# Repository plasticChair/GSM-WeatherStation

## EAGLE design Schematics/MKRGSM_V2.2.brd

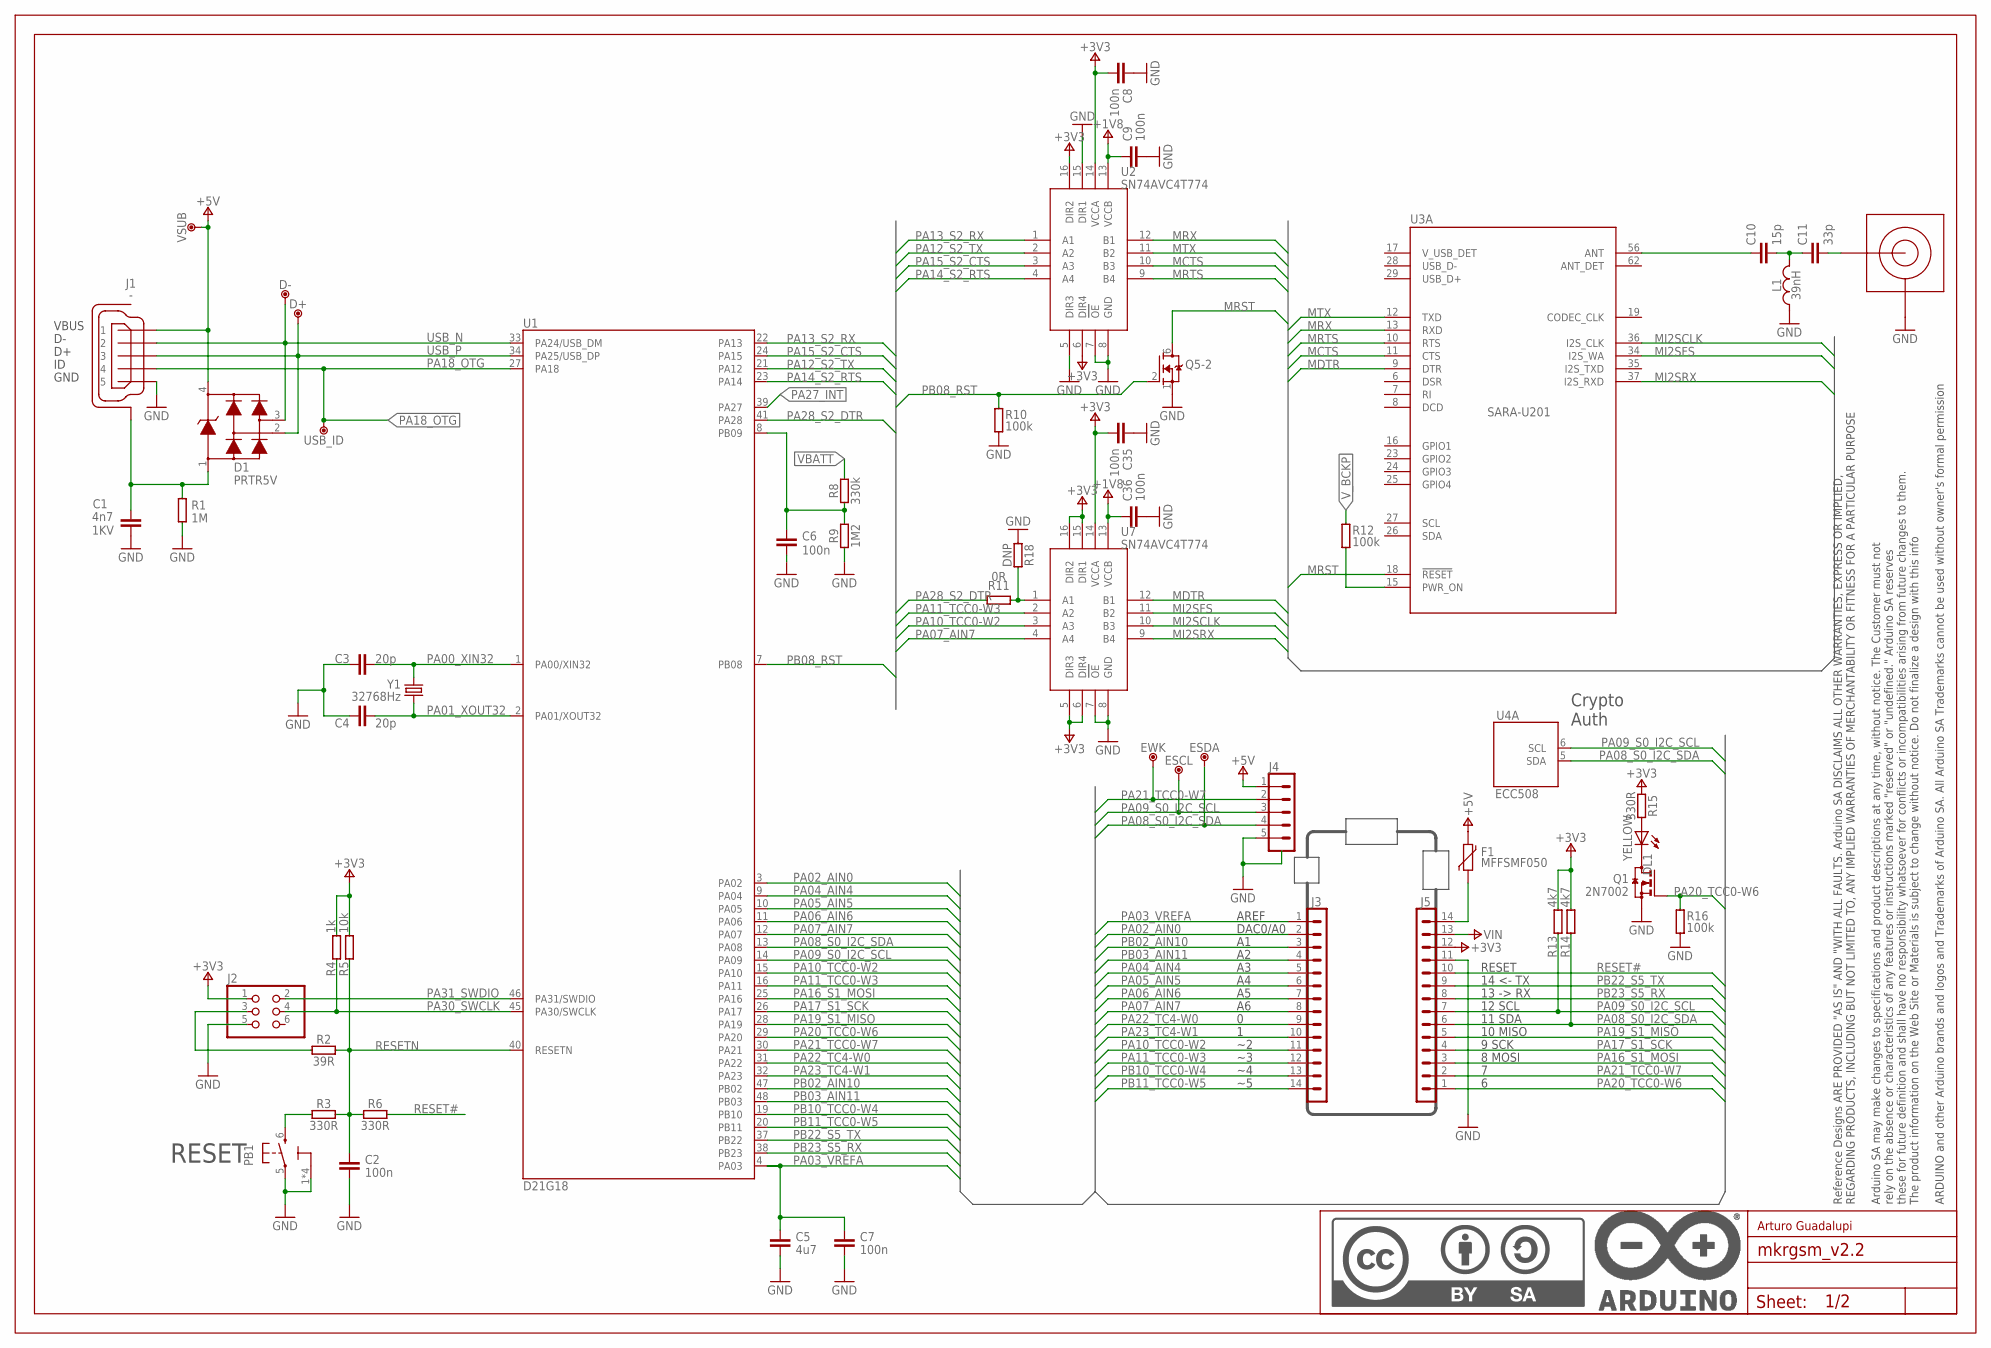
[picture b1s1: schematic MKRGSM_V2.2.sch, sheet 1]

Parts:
C1: 4n7; 0805-R2013X50N@1; VOLTAGE 1KV
C2, C6, C7, C8, C9, C35, C36: 100n; 0402-1005X55N
C3, C4: 20p; 0402-1005X55N
C5: 4u7; 0402-1005X55N
C10: 15p; 0402-1005X55N
C11: 33p; 0402-1005X55N
D1: PRTR5V; SOT190P230X110-4N
D+: DNP; TP-1.00MM
D-: DNP; TP-1.00MM
DL1: YELLOW; LEDC1608X80N-AK
ESCL: DNP; TP-1.00MM
ESDA: DNP; TP-1.00MM
EWK: DNP; TP-1.00MM
F1: MFFSMF050; 0603-1608X90N
FRAME1: DNP; FRAME
J1: -; ZX62-AB-5PA
J2: DNP; 2X3_SMT
J3, J5: -; 1X14_SMD_TH
J4: -; SM05B-SRSS-TB
J6: -; U.FL-R-SMT-1(60)
L1: 39nH; C0402
PB1: PTS820; C&K_PTS820_NO_HOLES
Q1: 2N7002; SOTFL50P160X78-3
Q5: 2N7002DW-7-FNO_PAD; PWR_SC70-6L2
R1: 1M; 0402-1005X55N
R2: 39R; 0402-1005X55N
R3, R6, R15: 330R; 0402-1005X55N
R4: 1k; 0402-1005X55N
R5: 10k; 0402-1005X55N
R8: 330k; 0402-1005X55N
R9: 1M2; 0402-1005X55N
R10, R12, R16: 100k; 0402-1005X55N
R11: 0R; 0402-1005X55N
R13, R14: 4k7; 0402-1005X55N
R18: DNP; 0402-1005X55N
U1: D21G18; QFN50P700X700X90-49XN-EPSQ515
U2, U7: SN74AVC4T774; RSV
U3: SARA-U201; SARA-96
U4: ECC508; SON50P300X200X60-9N-EP160X140
USB_ID: DNP; TP-1.00MM
VSUB: DNP; TP-1.00MM
Y1: 32768Hz; ABS07

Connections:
+1V8: C9.1, C36.1, U2.13 (VCCB), U7.13 (VCCB); also elsewhere on the board
+3V3: C8.2, C35.2, J2.1, J5.12, R4.2, R5.2, R13.2, R14.2, R15.1, U2.6 (DIR4), U2.14 (VCCA), U2.16 (DIR2), U7.5 (DIR3), U7.6 (DIR4), U7.14 (VCCA), U7.15 (DIR1), U7.16 (DIR2); also elsewhere on the board
+5V: D1.4, F1.2, J1.1, J4.1, VSUB.X; also elsewhere on the board
GND: C1.2, C2.2, C3.1, C4.1, C5.2, C6.2, C7.2, C8.1, C9.2, C35.1, C36.2, J1.5, J2.5, J4.5, J4.SH1 (SH), J4.SH2 (SH), J5.11, J6.GND1 (GND), J6.GND2 (GND), L1.1, PB1.1 (3), PB1.2 (3), PB1.3, PB1.4 (3), PB1.5 (1), Q1.S, Q5.1 (S), R1.1, R9.1, R10.1, R16.1, R18.1, U2.5 (DIR3), U2.7 (OE), U2.8 (GND), U2.15 (DIR1), U7.7 (OE), U7.8 (GND); also elsewhere on the board
MCTS: U2.10 (B3), U3.11 (CTS)
MDTR: U3.9 (DTR), U7.12 (B1)
MI2SCLK: U3.36 (I2S_CLK), U7.10 (B3)
MI2SFS: U3.34 (I2S_WA), U7.11 (B2)
MI2SRX: U3.37 (I2S_RXD), U7.9 (B4)
MRST: Q5.6 (D), U3.18 (!RESET)
MRTS: U2.9 (B4), U3.10 (RTS)
MRX: U2.12 (B1), U3.13 (RXD)
MTX: U2.11 (B2), U3.12 (TXD)
N17658775: PB1.6 (2), R3.1
unnamed: C1.1, D1.1, J1.6 (SH), J1.7 (SH), J1.8 (SH), J1.9 (SH), J1.10 (SH), J1.11 (SH), R1.2
unnamed: F1.1, J5.14
unnamed: J2.3, R2.1
unnamed: C10.1, U3.56 (ANT)
unnamed: C6.1, R8.1, R9.2, U1.8 (PB09)
unnamed: DL1.A, R15.2
unnamed: C11.2, J6.SIG
unnamed: R11.1, R18.2, U7.1 (A1)
unnamed: DL1.C, Q1.D
unnamed: R12.1, U3.15 (PWR_ON)
unnamed: C10.2, C11.1, L1.2
PA00_XIN32: C3.2, U1.1 (PA00/XIN32), Y1.2
PA01_XOUT32: C4.2, U1.2 (PA01/XOUT32), Y1.1
PA02_AIN0: J3.2, U1.3 (PA02)
PA03_VREFA: C5.1, C7.1, J3.1, U1.4 (PA03)
PA04_AIN4: J3.5, U1.9 (PA04)
PA05_AIN5: J3.6, U1.10 (PA05)
PA06_AIN6: J3.7, U1.11 (PA06)
PA07_AIN7: J3.8, U1.12 (PA07), U7.4 (A4)
PA08_S0_I2C_SDA: ESDA.X, J4.4, J5.6, R14.1, U1.13 (PA08), U4.5 (SDA); also elsewhere on the board
PA09_S0_I2C_SCL: ESCL.X, J4.3, J5.7, R13.1, U1.14 (PA09), U4.6 (SCL); also elsewhere on the board
PA10_TCC0-W2: J3.11, U1.15 (PA10), U7.3 (A3)
PA11_TCC0-W3: J3.12, U1.16 (PA11), U7.2 (A2)
PA12_S2_TX: U1.21 (PA12), U2.2 (A2)
PA13_S2_RX: U1.22 (PA13), U2.1 (A1)
PA14_S2_RTS: U1.23 (PA14), U2.4 (A4)
PA15_S2_CTS: U1.24 (PA15), U2.3 (A3)
PA16_S1_MOSI: J5.3, U1.25 (PA16)
PA17_S1_SCK: J5.4, U1.26 (PA17)
PA18_OTG: J1.4, U1.27 (PA18), USB_ID.X; also elsewhere on the board
PA19_S1_MISO: J5.5, U1.28 (PA19)
PA20_TCC0-W6: J5.1, Q1.G, R16.2, U1.29 (PA20)
PA21_TCC0-W7: EWK.X, J4.2, J5.2, U1.30 (PA21)
PA22_TC4-W0: J3.9, U1.31 (PA22)
PA23_TC4-W1: J3.10, U1.32 (PA23)
PA27_INT: U1.39 (PA27); also elsewhere on the board
PA28_S2_DTR: R11.2, U1.41 (PA28)
PA30_SWCLK: J2.4, R4.1, U1.45 (PA30/SWCLK)
PA31_SWDIO: J2.2, U1.46 (PA31/SWDIO)
PB02_AIN10: J3.3, U1.47 (PB02)
PB03_AIN11: J3.4, U1.48 (PB03)
PB08_RST: Q5.2 (G), R10.2, U1.7 (PB08)
PB10_TCC0-W4: J3.13, U1.19 (PB10)
PB11_TCC0-W5: J3.14, U1.20 (PB11)
PB22_S5_TX: J5.9, U1.37 (PB22)
PB23_S5_RX: J5.8, U1.38 (PB23)
RESET#: J5.10, R6.2
RESETN: C2.1, R2.2, R3.2, R5.1, R6.1, U1.40 (RESETN)
USB_N: D1.3, D-.X, J1.2, U1.33 (PA24/USB_DM); also elsewhere on the board
USB_P: D1.2, D+.X, J1.3, U1.34 (PA25/USB_DP); also elsewhere on the board
VBATT: R8.2; also elsewhere on the board
VIN: J5.13; also elsewhere on the board
V_BCKP: R12.2; also elsewhere on the board

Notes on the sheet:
14 <- TX
13 -> RX
12 SCL
RESET
11 SDA
8 MOSI
9 SCK
10 MISO
AREF
DAC0/A0
Crypto Auth
Arturo Guadalupi

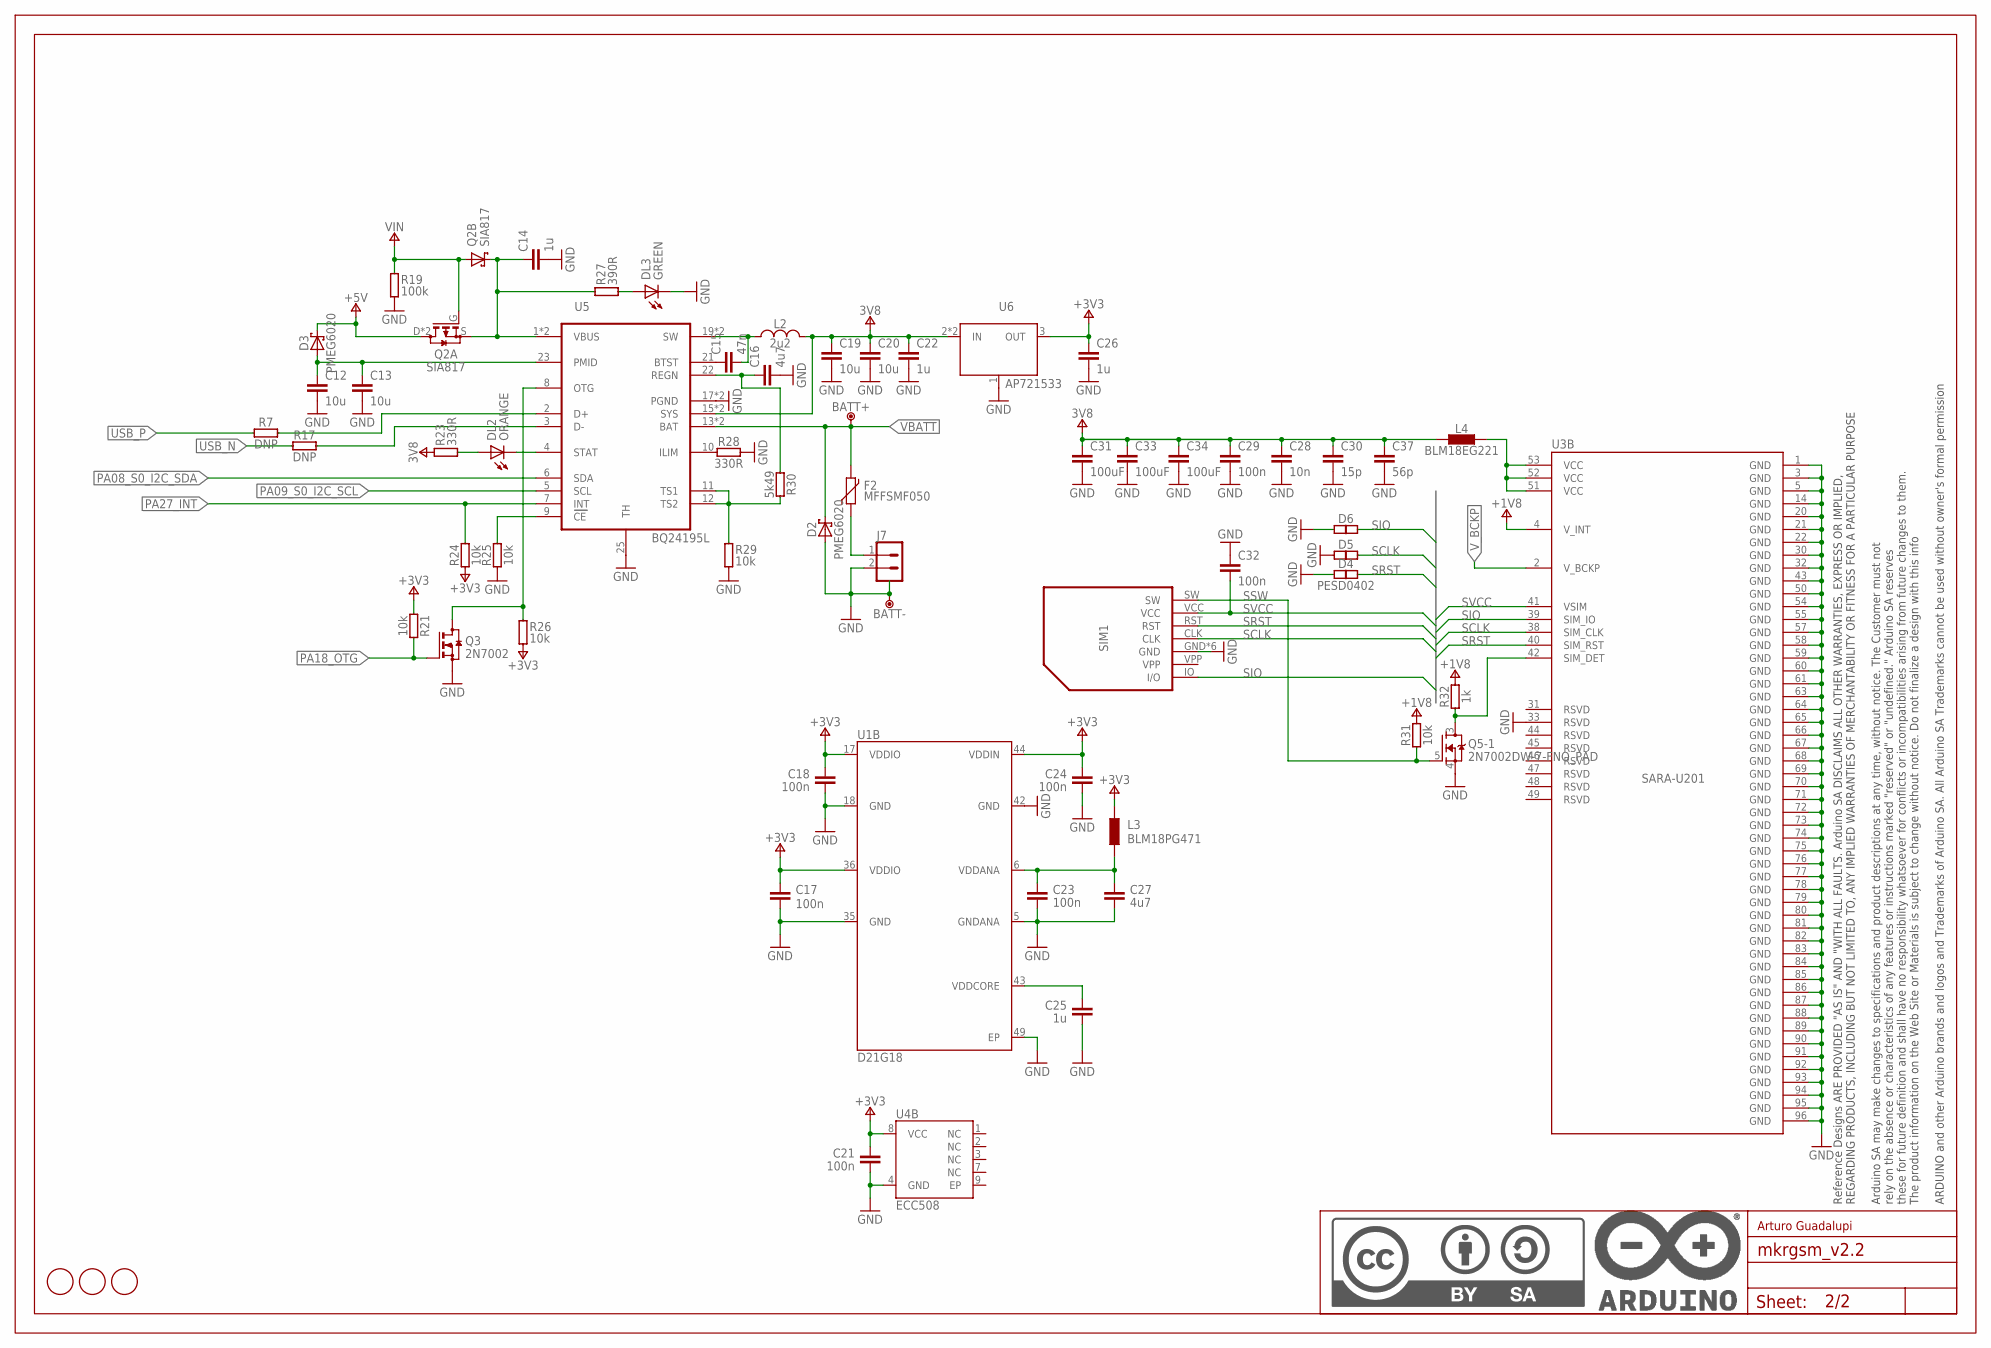
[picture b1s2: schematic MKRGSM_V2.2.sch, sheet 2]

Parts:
BATT+: DNP; TP-1.00MM
BATT-: DNP; TP-1.00MM
C12, C13, C19, C20: 10u; 0603-1608X90N
C14, C22, C25, C26: 1u; 0402-1005X55N
C15: 47n; 0402-1005X55N
C16: 4u7; 0402-1005X55N
C17, C18, C21, C23, C24, C29, C32: 100n; 0402-1005X55N
C27: 4u7; 0603-1608X90N
C28: 10n; 0402-1005X55N
C30: 15p; 0402-1005X55N
C31, C33, C34: 100uF; C1206
C37: 56p; 0402-1005X55N
D2, D3: PMEG6020; SODFL3517X110N
D4, D5, D6: PESD0402; 0402-1005X55N
DL2: ORANGE; LEDC1608X80N-AK
DL3: GREEN; LEDC1608X80N-AK
F2: MFFSMF050; 0603-1608X90N
FD1, FD2, FD3: DNP; FD-1-1.5
FRAME2: DNP; FRAME
J7: -; JST-S2B-PH-SM4-TB
L2: 2u2; SRP4020
L3: BLM18PG471; 0603-1608X90N
L4: BLM18EG221; 0603-1608X90N
Q2: SIA817; SON65P205X205X75-8N-MWSD
Q3: 2N7002; SOTFL50P160X78-3
Q5: 2N7002DW-7-FNO_PAD; PWR_SC70-6L2
R7, R17: DNP; 0402-1005X55N
R19: 100k; 0402-1005X55N
R21, R24, R25, R26, R29, R31: 10k; 0402-1005X55N
R23, R28: 330R; 0402-1005X55N
R27: 390R; 0402-1005X55N
R30: 5k49; 0402-1005X55N
R32: 1k; 0402-1005X55N
SIM1: -; MICROSIM8
U1: D21G18; QFN50P700X700X90-49XN-EPSQ515
U3: SARA-U201; SARA-96
U4: ECC508; SON50P300X200X60-9N-EP160X140
U5: BQ24195L; QFN24
U6: AP721533; SOT89-3L

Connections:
+1V8: R31.2, R32.2, U3.4 (V_INT); also elsewhere on the board
+3V3: C17.1, C18.1, C21.1, C24.1, C26.1, L3.1, R21.1, R24.1, R26.1, U1.17 (VDDIO), U1.36 (VDDIO), U1.44 (VDDIN), U4.8 (VCC), U6.3 (OUT); also elsewhere on the board
+3V8: C19.1, C20.1, C22.1, C28.1, C29.1, C30.1, C31.1, C33.1, C34.1, C37.1, L2.2, L4.1, R23.2, U5.15 (SYS), U5.16 (SYS), U6.2 (IN), U6.TH (IN)
+5V: D3.C, Q2.D, Q2.D2 (D); also elsewhere on the board
GND: BATT-.X, C12.2, C13.2, C14.2, C16.2, C17.2, C18.2, C19.2, C20.2, C21.2, C22.2, C23.2, C24.2, C25.2, C26.2, C27.2, C28.2, C29.2, C30.2, C31.2, C32.1, C33.2, C34.2, C37.2, D2.A, D4.1, D5.1, D6.1, DL3.C, J7.2, J7.3 (SH), J7.4 (SH), Q3.S, Q5.4 (S), R19.1, R25.1, R28.2, R29.1, SIM1.GND, SIM1.SH1 (GND), SIM1.SH2 (GND), SIM1.SH3 (GND), SIM1.SH4 (GND), SIM1.SH5 (GND), U1.5 (GNDANA), U1.18 (GND), U1.35 (GND), U1.42 (GND), U1.49 (EP), U3.1 (GND), U3.3 (GND), U3.5 (GND), U3.14 (GND), U3.20 (GND), U3.21 (GND), U3.22 (GND), U3.30 (GND), U3.32 (GND), U3.33 (RSVD), U3.43 (GND), U3.50 (GND), U3.54 (GND), U3.55 (GND), U3.57 (GND), U3.58 (GND), U3.59 (GND), U3.60 (GND), U3.61 (GND), U3.63 (GND), U3.64 (GND), U3.65 (GND), U3.66 (GND), U3.67 (GND), U3.68 (GND), U3.69 (GND), U3.70 (GND), U3.71 (GND), U3.72 (GND), U3.73 (GND), U3.74 (GND), U3.75 (GND), U3.76 (GND), U3.77 (GND), U3.78 (GND), U3.79 (GND), U3.80 (GND), U3.81 (GND), U3.82 (GND), U3.83 (GND), U3.84 (GND), U3.85 (GND), U3.86 (GND), U3.87 (GND), U3.88 (GND), U3.89 (GND), U3.90 (GND), U3.91 (GND), U3.92 (GND), U3.93 (GND), U3.94 (GND), U3.95 (GND), U3.96 (GND), U4.4 (GND), U5.17 (PGND), U5.18 (PGND), U5.25 (TH), U6.1 (GND/ADJ); also elsewhere on the board
N17798864: DL2.A, R23.1
N17834267: DL3.A, R27.1
N17852357: C23.1, C27.1, L3.2, U1.6 (VDDANA)
N17852431: C25.1, U1.43 (VDDCORE)
unnamed: F2.1, J7.1
unnamed: Q5.3 (D), R32.1, U3.42 (SIM_DET)
unnamed: L4.2, U3.51 (VCC), U3.52 (VCC), U3.53 (VCC)
unnamed: C15.2, L2.1, U5.19 (SW), U5.20 (SW)
unnamed: R7.2, U5.2 (D+)
unnamed: C14.1, Q2.K (C), Q2.K2 (C), Q2.S, R27.2, U5.1 (VBUS), U5.24 (VBUS)
unnamed: C15.1, U5.21 (BTST)
unnamed: R28.1, U5.10 (ILIM)
unnamed: R17.2, U5.3 (D-)
unnamed: C16.1, R30.1, U5.22 (REGN)
unnamed: Q3.D, R26.2, U5.8 (OTG)
unnamed: R29.2, R30.2, U5.11 (TS1), U5.12 (TS2)
unnamed: R25.2, U5.9 (CE)
PA08_S0_I2C_SDA: U5.6 (SDA); also elsewhere on the board
PA09_S0_I2C_SCL: U5.5 (SCL); also elsewhere on the board
PA18_OTG: Q3.G, R21.2; also elsewhere on the board
PA27_INT: R24.2, U5.7 (INT); also elsewhere on the board
SCLK: D5.2, SIM1.CLK, U3.38 (SIM_CLK)
SIO: D6.2, SIM1.IO (I/O), U3.39 (SIM_IO)
SRST: D4.2, SIM1.RST, U3.40 (SIM_RST)
SSW: Q5.5 (G), R31.1, SIM1.SW
STAT: DL2.C, U5.4 (STAT)
SVCC: C32.2, SIM1.VCC, U3.41 (VSIM)
USB_N: R17.1; also elsewhere on the board
USB_P: R7.1; also elsewhere on the board
VBATT: BATT+.X, D2.C, F2.2, U5.13 (BAT), U5.14 (BAT); also elsewhere on the board
VIN: Q2.A, Q2.G, R19.2; also elsewhere on the board
VUSB1: C12.1, C13.1, D3.A, U5.23 (PMID)
V_BCKP: U3.2 (V_BCKP); also elsewhere on the board

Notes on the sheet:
Arturo Guadalupi

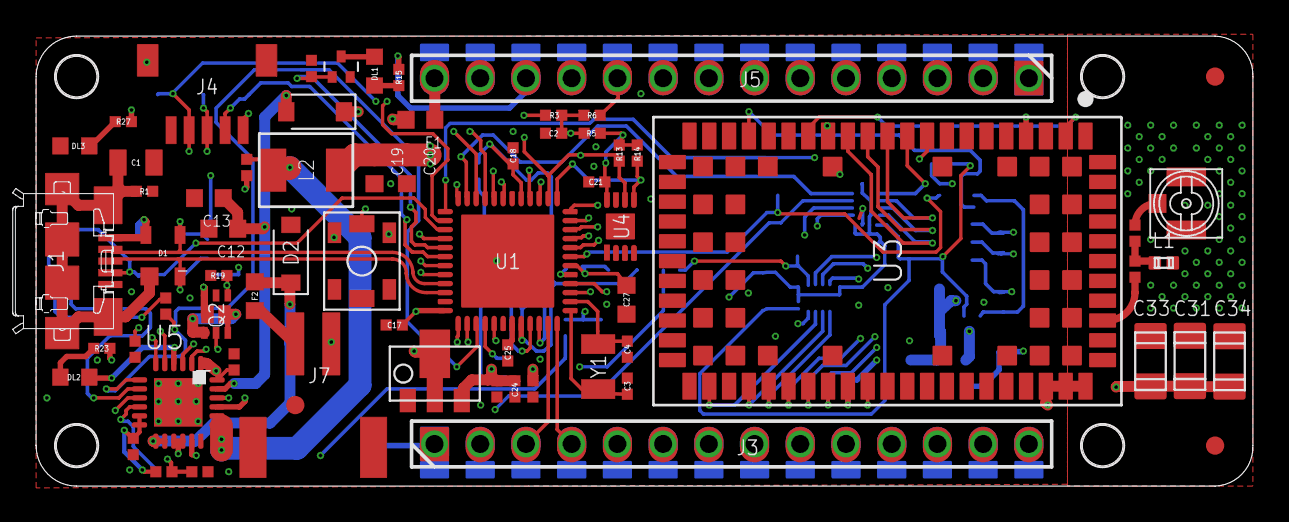
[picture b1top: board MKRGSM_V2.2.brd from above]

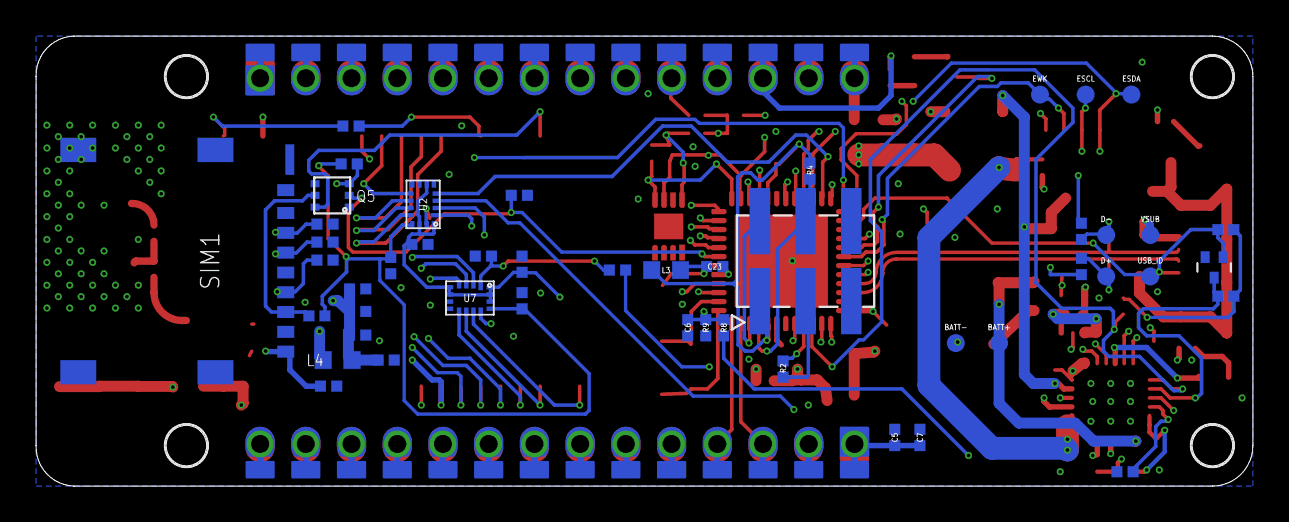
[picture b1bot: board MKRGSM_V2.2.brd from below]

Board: 4 copper layers, 67.6 x 25.0 mm, 121 parts (39 on the bottom side), 92 nets.

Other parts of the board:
U$5, U$6, U$7, U$8: MH_RND_F_2.2MM_NM

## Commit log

2019-05-16 init commit of git. Working board and website
2019-10-07 Commit before server update
2019-10-24 commit before more

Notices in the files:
Schematics/MKRGSM_V2.2.brd:
Copyright (c) 2016-2017 Arduino LLC.  All right reserved. EAGLE Design Rules
parts and their libraries:
Arduino-ucs: Copyright (c) 2016-2017 Arduino LLC.  All right reserved.
